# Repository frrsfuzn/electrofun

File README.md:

# ElectroFun
Welcome to my project of electronic. Hopefully my project can be useful for all of you :)

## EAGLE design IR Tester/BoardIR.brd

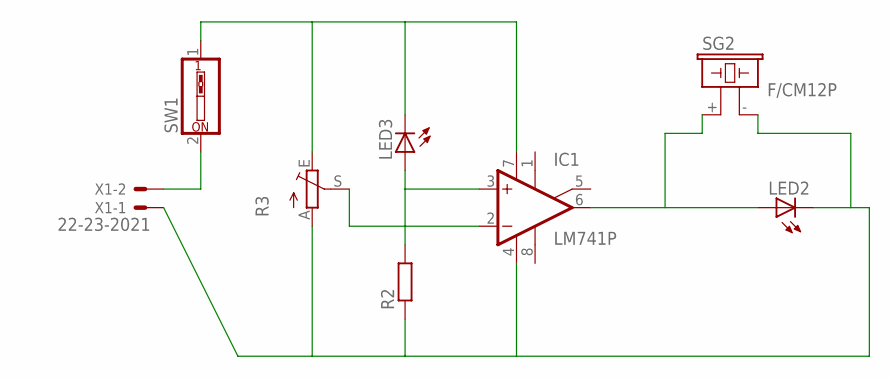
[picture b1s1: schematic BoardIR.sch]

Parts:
IC1: LM741P; DIL08
LED2, LED3: LED5MM
R2: R-EU_0204/5; 0204/5
R3: TRIM_EU-CA6V; CA6V
SG2: F/CM12P
SW1: SW_DIP-1; EDG-01
X1: 22-23-2021

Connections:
unnamed: IC1.3 (+IN), LED3.A, R2.2
unnamed: IC1.2 (-IN), R3.S
unnamed: IC1.4 (V-), LED2.K (C), R2.1, R3.A, SG2.- (2), X1.1
unnamed: IC1.7 (V+), LED3.K (C), R3.E, SW1.1
unnamed: IC1.6 (OUT), LED2.A, SG2.+ (1)
unnamed: SW1.2, X1.2

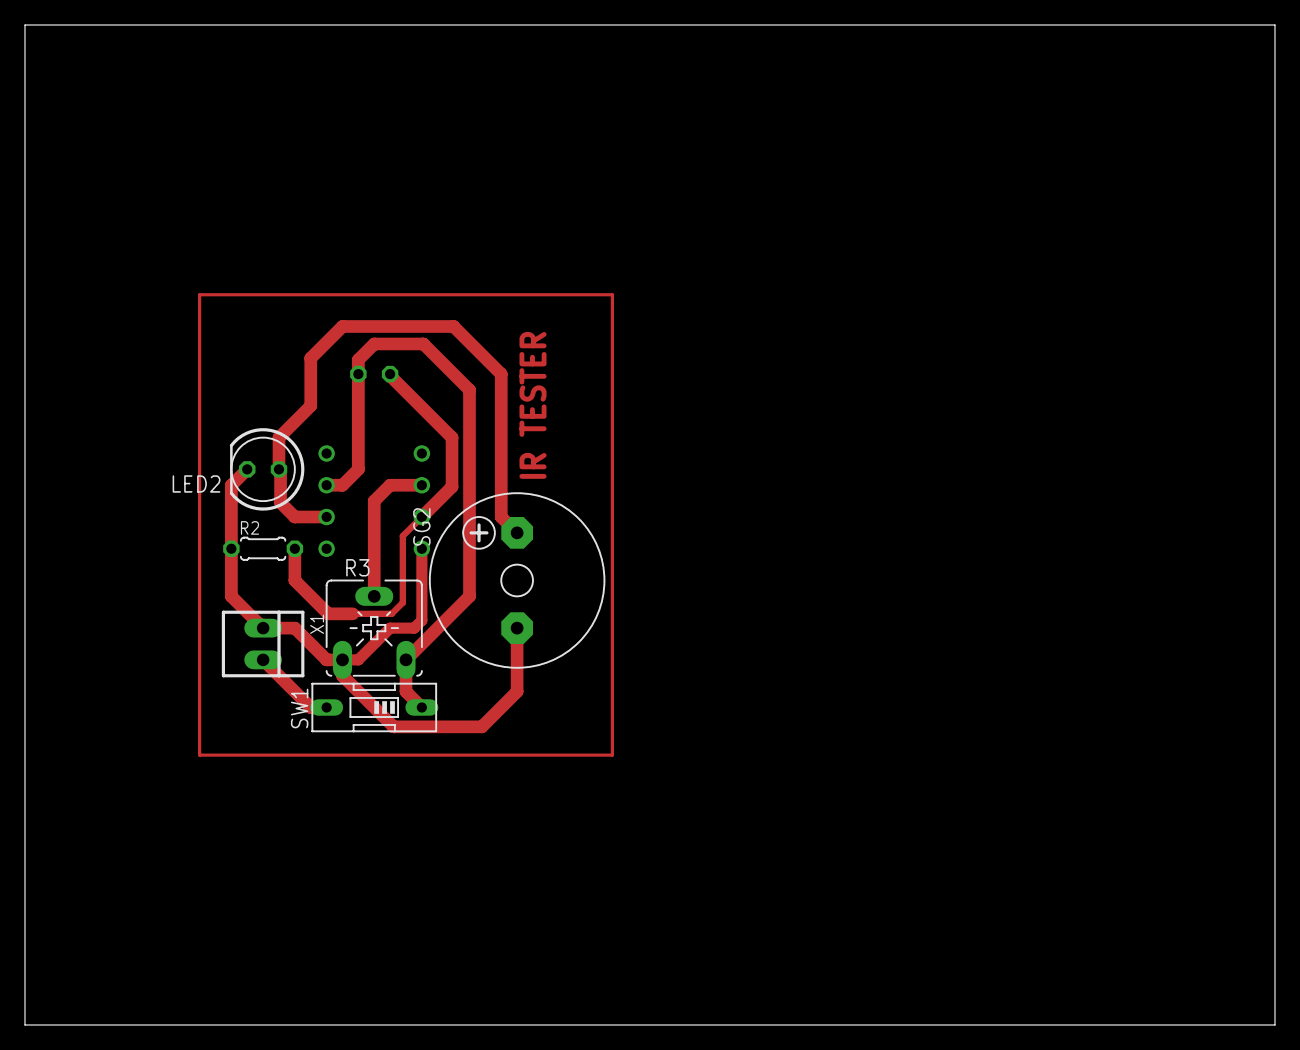
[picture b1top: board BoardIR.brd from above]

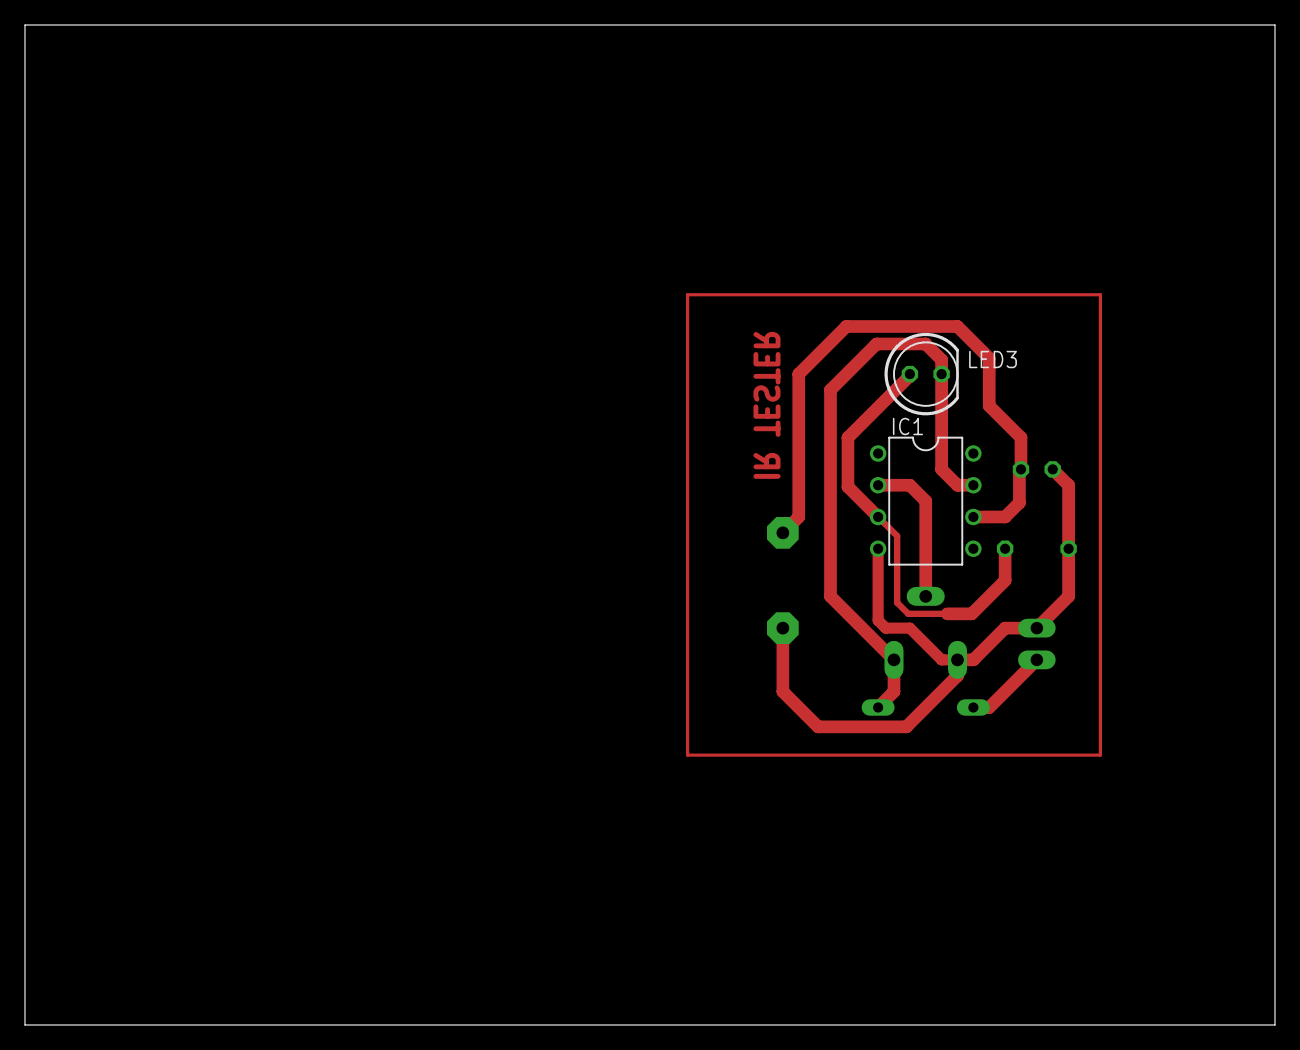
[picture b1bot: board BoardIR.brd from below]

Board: 2 copper layers, 100.0 x 80.0 mm, 8 parts (2 on the bottom side), 6 nets.

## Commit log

2019-05-18 Add files via upload
    IR Tester - Berfungsi untuk mendeteksi cahaya inframerah dari remote, led, dan lain-lain
